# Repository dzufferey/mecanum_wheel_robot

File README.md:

# Mecanum wheels robot

A small omnidirectional wheeled robot.

The robot is designed as part of a series of tutorials covering: CAD, prototyping, and programming.

The project is split among the following directories:
- [body](body)
- [code](code)
- [pcb](pcb)

Not everything is in this repository.
You will also need:
- a model for the [mecanum wheels](https://github.com/dzufferey/scadla/blob/master/src/main/scala/scadla/examples/MecanumWheel.scala), or [alternatives](https://www.thingiverse.com/search?q=mecanum) like [this](https://www.thingiverse.com/thing:1203230)
- a case for Raspberry Pi (look on [Thingiverse](http://www.thingiverse.com/))

The [HOWTO.md](HOWTO.md) file describe how to put things together.

## Attributions

- [Bosch Blue 10.8 volt battery container](https://www.thingiverse.com/thing:1246842) by topias5 is licensed under the CC-BY-NC license.
- references and model for [A4988 Stepper Motor Driver Carrier, Black Edition](https://www.pololu.com/product/2128), license unclear ...
- [KiCAD module for the stepper dirvers](https://github.com/jharvey/Cinch_enclosure_template/tree/master/KICAD_Project/PCB-modules/pololu) by Jared Harvey, license unclear ...
- [rpi3-bottom_netfabb.stl](https://www.thingiverse.com/thing:2413372) by sachingm is licensed under CC-BY.

## License

The content of this project itself is licensed under the [Creative Commons Attribution 3.0 license](http://creativecommons.org/licenses/by/3.0/us/deed.en_US), and the source code in the `code` folder is licensed under the [MIT license](http://opensource.org/licenses/mit-license.php).

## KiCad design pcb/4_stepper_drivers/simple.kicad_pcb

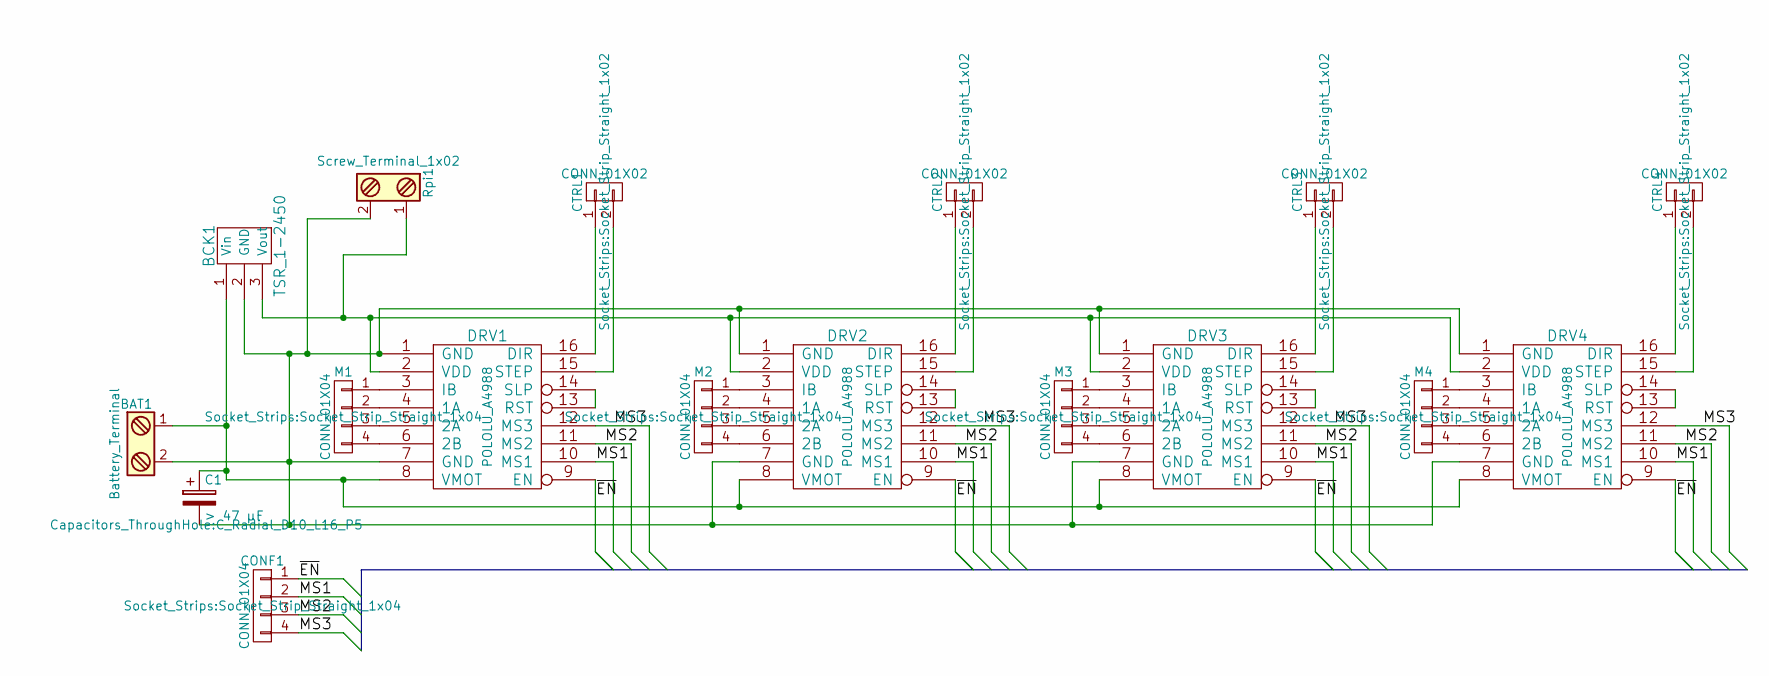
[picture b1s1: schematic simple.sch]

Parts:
BAT1: Battery_Terminal; TerminalBlock_Pheonix_MKDS1.5-2pol
BCK1: TSR_1-2450; TO-220_Neutral123_PadsOnly
C1: > 47 µF; C_Radial_D10_L16_P5
CONF1: CONN_01X04; Socket_Strip_Straight_1x04
CTRL1, CTRL2, CTRL3, CTRL4: CONN_01X02; Socket_Strip_Straight_1x02
DRV1, DRV2, DRV3, DRV4: POLOLU_A4988; Pololu_a4988
M1, M2, M3, M4: CONN_01X04; Socket_Strip_Straight_1x04
Rpi1: Screw_Terminal_1x02; TerminalBlock_Pheonix_MPT-2.54mm_2pol

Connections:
/MS1: CONF1.2, DRV1.10 (MS1), DRV2.10 (MS1), DRV3.10 (MS1), DRV4.10 (MS1)
/MS2: CONF1.3, DRV1.11 (MS2), DRV2.11 (MS2), DRV3.11 (MS2), DRV4.11 (MS2)
/MS3: CONF1.4, DRV1.12 (MS3), DRV2.12 (MS3), DRV3.12 (MS3), DRV4.12 (MS3)
/~EN: CONF1.1, DRV1.9 (EN), DRV2.9 (EN), DRV3.9 (EN), DRV4.9 (EN)
unnamed: BAT1.1 (+), BCK1.1 (Vin), C1.1, DRV1.8 (VMOT), DRV2.8 (VMOT), DRV3.8 (VMOT), DRV4.8 (VMOT)
unnamed: BAT1.2 (-), BCK1.2 (GND), C1.2, DRV1.1 (GND), DRV1.7 (GND), DRV2.1 (GND), DRV2.7 (GND), DRV3.1 (GND), DRV3.7 (GND), DRV4.1 (GND), DRV4.7 (GND), Rpi1.2
unnamed: BCK1.3 (Vout), DRV1.2 (VDD), DRV2.2 (VDD), DRV3.2 (VDD), DRV4.2 (VDD), Rpi1.1
unnamed: CTRL1.1, DRV1.16 (DIR)
unnamed: CTRL1.2, DRV1.15 (STEP)
unnamed: CTRL2.1, DRV2.16 (DIR)
unnamed: CTRL2.2, DRV2.15 (STEP)
unnamed: CTRL3.1, DRV3.16 (DIR)
unnamed: CTRL3.2, DRV3.15 (STEP)
unnamed: CTRL4.1, DRV4.16 (DIR)
unnamed: CTRL4.2, DRV4.15 (STEP)
unnamed: DRV1.3 (IB), M1.1
unnamed: DRV1.4 (1A), M1.2
unnamed: DRV1.5 (2A), M1.3
unnamed: DRV1.6 (2B), M1.4
unnamed: DRV1.13 (RST), DRV1.14 (SLP)
unnamed: DRV2.3 (IB), M2.1
unnamed: DRV2.4 (1A), M2.2
unnamed: DRV2.5 (2A), M2.3
unnamed: DRV2.6 (2B), M2.4
unnamed: DRV2.13 (RST), DRV2.14 (SLP)
unnamed: DRV3.3 (IB), M3.1
unnamed: DRV3.4 (1A), M3.2
unnamed: DRV3.5 (2A), M3.3
unnamed: DRV3.6 (2B), M3.4
unnamed: DRV3.13 (RST), DRV3.14 (SLP)
unnamed: DRV4.3 (IB), M4.1
unnamed: DRV4.4 (1A), M4.2
unnamed: DRV4.5 (2A), M4.3
unnamed: DRV4.6 (2B), M4.4
unnamed: DRV4.13 (RST), DRV4.14 (SLP)

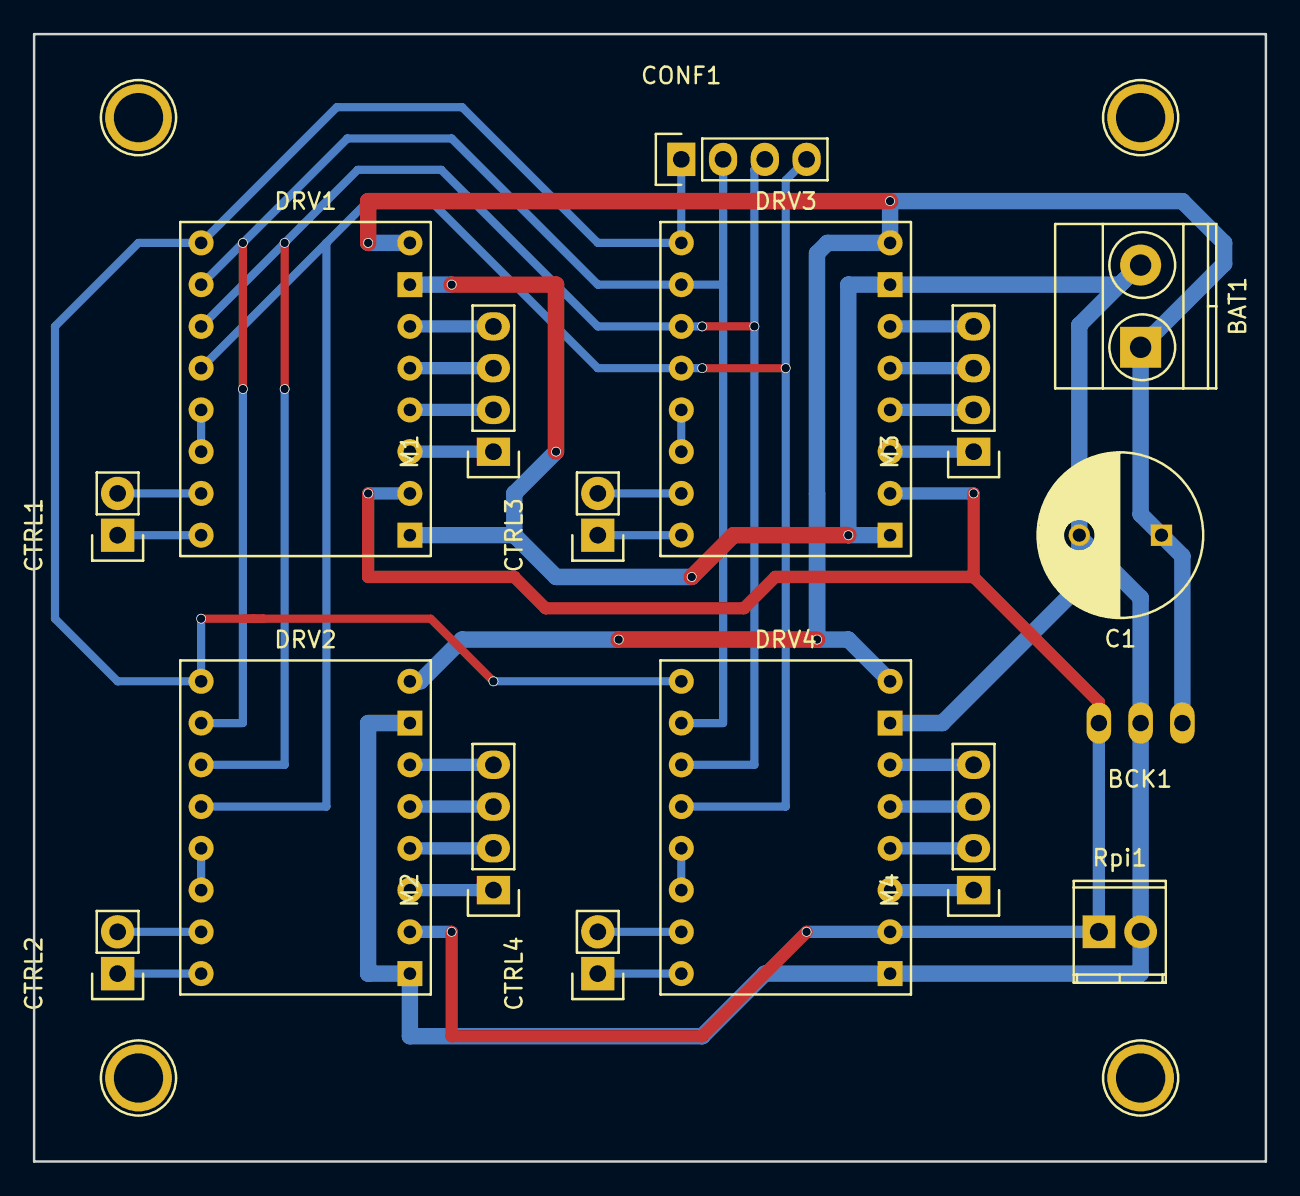
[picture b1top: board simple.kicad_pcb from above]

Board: 2 copper layers, 74.9 x 68.6 mm, 17 parts (0 on the bottom side), 35 nets.

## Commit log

2017-08-14 adding the source files
2017-08-14 some more description
2017-09-04 absolute -> relative paths
2017-09-04 footprint lib as project specific lib
2017-09-19 adding some more files
